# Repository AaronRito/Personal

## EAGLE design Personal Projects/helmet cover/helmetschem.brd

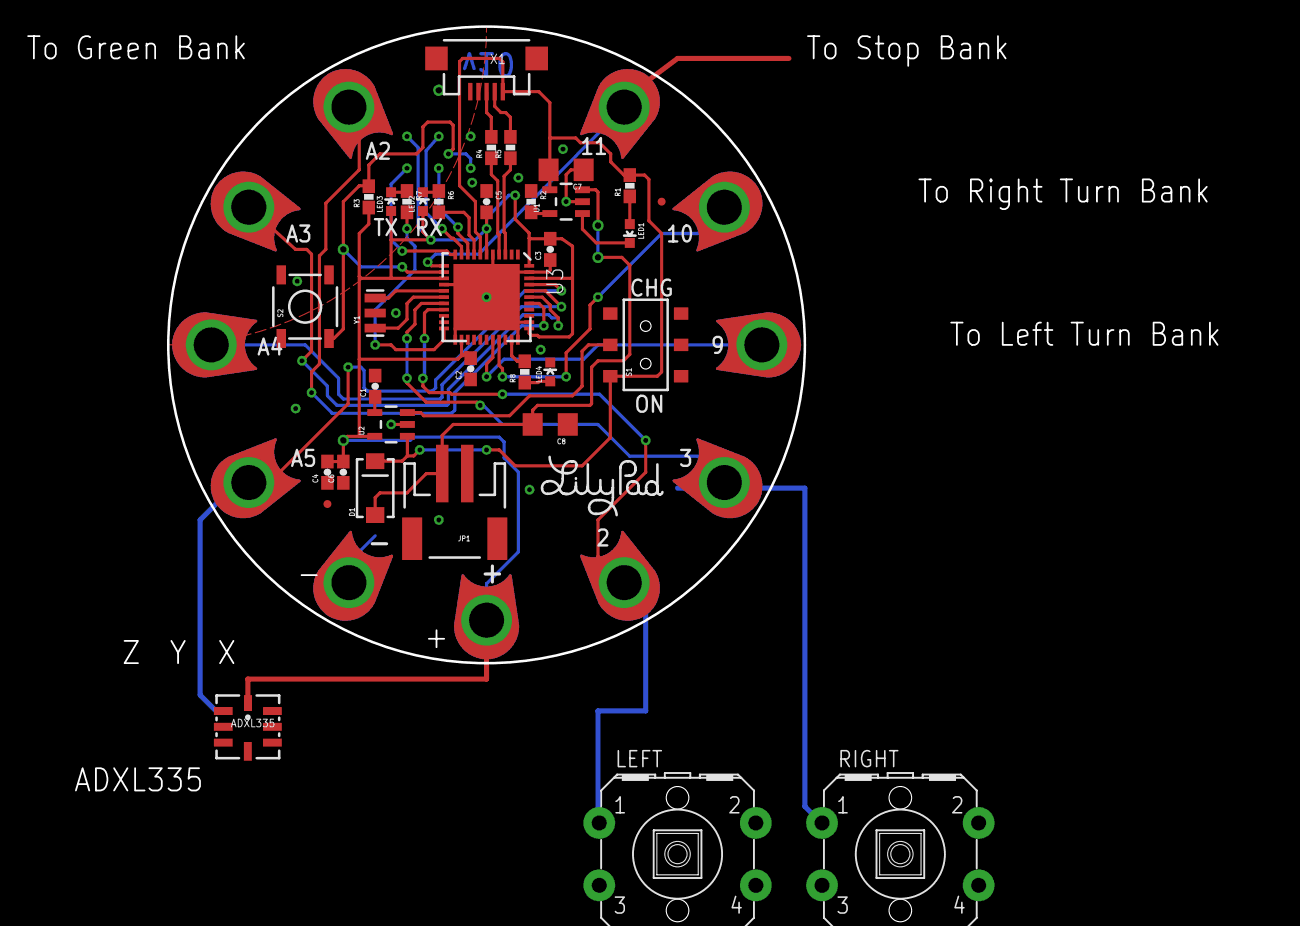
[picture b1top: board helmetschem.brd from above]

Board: 2 copper layers, 50.8 x 50.8 mm, 47 parts (1 on the bottom side), 31 nets.

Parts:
+: SEWTAP9; PETAL-LONG-1-2SIDE
-: SEWTAP9; PETAL-LONG-1-2SIDE
A2, A3, A4, A5: SEWTAP9; PETAL-LONG-1-2SIDE
ADXL335: ADXL193
C1: 470pF; 0603-CAP
C2, C3, C4: .1uF; 0603-CAP
C5: 1uF; 0603-CAP
C6: 4.7uF; 0603-CAP
C7, C8: 4.7uF; 1206
D1: B340A; SMA-DIODE
D5, D6, D9, D10, D11: SEWTAP9; PETAL-LONG-1-2SIDE
JP1: JST-2; JST-2-SMD
JP2, JP3: FIDUCIALUFIDUCIAL; MICRO-FIDUCIAL
LED1, LED2, LED3, LED4: RED; LED-0603
LEFT: B3F-40XX-ROUND
R1, R6, R7, R8: 330; 0603-RES
R2, R3: 10k; 0603-RES
R4, R5: 22; 0603-RES
RIGHT: B3F-40XX-ROUND
S1: SWITCH-DPDTSMD; AYZ0202
S2: !RESET; TACTILE_SWITCH_SMD
U1: MCP73831; SOT23-5
U2: MIC5219; SOT23-5
U3: ATMEGA32U4QFN; QFN-44
U$1: LOGO-LPLPA; LOGO-LPA
U$13: LOGO-LPLP; LOGO-LILYPAD
X1: USB-MICROB
Y1: 8MHz; RESONATOR-SMD

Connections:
3.3V: +.1, C2.2, C3.2, C4.2, C5.2, C6.2, LED2.A, LED3.A, R3.1, U2.5, U3.6, U3.14, U3.24, U3.34, U3.42, U3.44
5V: C7.2, D1.C, R1.2, S1.1, U1.4, U2.1, U3.7, X1.VBUS
D+: R4.1, U3.4
D-: R5.1, U3.3
GND: -.1, C1.2, C2.1, C3.1, C4.1, C5.1, C6.1, C7.1, C8.1, JP1.1, LED4.C, R2.1, S1.3, S2.1, U1.2, U2.2, U3.5, U3.15, U3.23, U3.33, U3.35, U3.43, U3.EPAD, X1.GND, X1.MT1, X1.MT2, Y1.2
unnamed: LED2.C, R6.1
unnamed: S1.2, U2.3
unnamed: LED1.A, R1.1
unnamed: LED1.C, U1.1
unnamed: U3.17, Y1.1
unnamed: R2.2, U1.5
unnamed: U3.16, Y1.3
unnamed: C1.1, U2.4
unnamed: D11.1, U3.12
unnamed: D10.1, U3.30
unnamed: D5.1, U3.19
unnamed: D6.1, U3.18
unnamed: A5.1, U3.41
unnamed: A4.1, U3.40
unnamed: A3.1, U3.39
unnamed: A2.1, U3.38
unnamed: LED4.A, R8.1
unnamed: R5.2, X1.D-
unnamed: R4.2, X1.D+
unnamed: LED3.C, R7.1
RESET: R3.2, S2.3, U3.13
RX_LED: R6.2, U3.8
S$4: D9.1, U3.29
TX_LED: R7.2, U3.22
USER_LED: R8.2, U3.32
V_BATT: C8.2, D1.A, JP1.2, U1.3

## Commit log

2018-11-01 bakcing up
    some older personal projects

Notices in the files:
parts and their libraries:
SparkFun-DigitalIC: Licensing: CC v3.0 Share-Alike You are welcome to use this library for commercial purposes.
SparkFun-Sensors: Licensing: Creative Commons ShareAlike 4.0 International - https://creativecommons.org/licenses/by-sa/4.0
